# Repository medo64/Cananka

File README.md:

[Cananka](https://medo64.com/cananka/)
======================================

Cananka allows for the computer control of a CAN bus. The control of device is
possible via serial port (SLCAN compatible, Windows/Linux) or via SocketCAN
network driver (Linux). More information about the SLCAN protocol is available
in a [separate document](PROTOCOL.md).

Features:
* USB serial device supporting SLCAN interface
* Supports 1 Mbps CAN bus operation
* Fully isolated (1 kV)
* Does not require CAN bus power supply (onboard DC-to-DC converter)
* 3.81 mm strip headers CAN bus connector
* USB 2.0 interface (type B)

The following hardware version are also available:
* [Mini](https://github.com/medo64/CanankaMini) (USB A connector, non-isolated, and without a case)
* [Framework Expansion Card](https://github.com/medo64/CanankaFEC) (non-isolated, in framework expansion card format)
* [HAT](https://github.com/medo64/CanankaHAT) (intended for Raspberry Pi)

The following additional repositories might be of interest:
* [Firmware](https://github.com/medo64/Cananka.Firmware)
* [Protocol](https://github.com/medo64/Cananka.Firmware/blob/main/PROTOCOL.md)
* [Test software](https://github.com/medo64/Cananka.Software)

---
*You can check my blog and other projects at [www.medo64.com](https://medo64.com/electronics/).*

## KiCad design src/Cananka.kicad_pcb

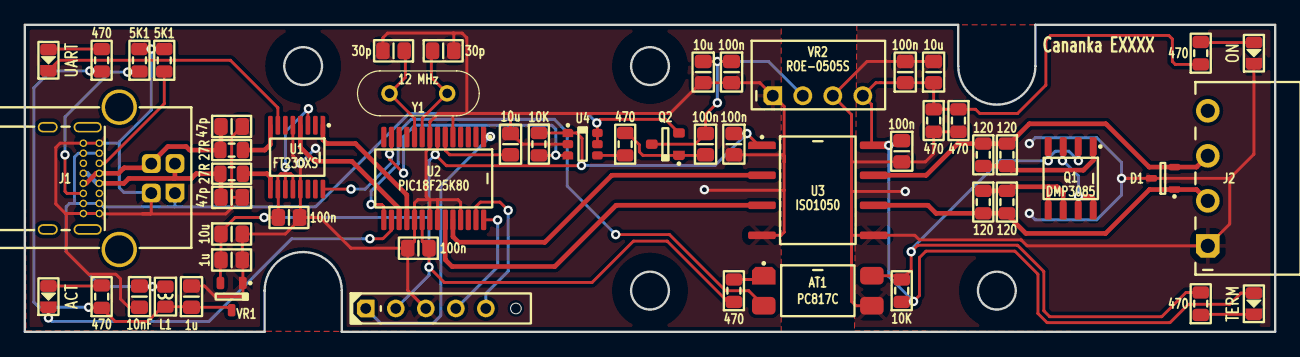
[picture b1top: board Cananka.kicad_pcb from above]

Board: 2 copper layers, 105.8 x 26.0 mm, 55 parts (0 on the bottom side), 40 nets.

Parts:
AT1: PC817C; AT Optocoupler 1ch 80kHz 5000V [817C] (SOP-4)
C1, C2: 30p; C (0805)
C3, C4: 47p; C (0805)
C5: 10nF; C (0805)
C6, C7, C8, C9, C10, C11, C12: 100n; C (0805)
C13, C14: 1u; C (0805)
C15, C16, C17, C18: 10u; C (0805)
D1: PESD24VL2BT; D TVS 24V [PESD24VL2BT,215] (SOT23-3)
DS1: ACT; DS (0805)
DS2: UART; DS (0805)
DS3: TERM; DS (0805)
DS4: ON; DS (0805)
ICSP: Microchip PIC; ICSP PIC Pogo (6w)
J1: USB4085 B1HSW6; J USB BC 2.0 Receptacle (4-16w)
J2: MC 1,5/4; J Phoenix MC [CAN] (4w)
L1: 1u; L (0805)
Q1: DMP3085; Q MOSFET-P x2 (SO-8)
Q2: BSS84; Q MOSFET-P (SOT23-3)
R1, R2: 27R; R (0805)
R3, R4, R5, R6: 120; R (0805)
R7, R8, R9, R10, R11, R12, R13, R14: 470; R (0805)
R15, R16: 5K1; R (0805)
R17, R18: 10K; R (0805)
U1: FT230XS; U Transceiver UART [FT230XS] (SSOP-16)
U2: PIC18F25K80; U Micro [PIC18F25K80] (SSOP-28)
U3: ISO1050; U Transceiver CAN Isolated [ISO1050DUBR] (SOP-8)
U4: 74LVC1T45; U LevelTranslator [74LVC1T45] (SOT23-6)
VR1: MCP1700; VR Linear 3.3V 250mA [MCP1700] (SOT-23)
VR2: ROE-0505S; VR DC-DC Isolated [ROE-0505S] (4w)
Y1: 12 MHz; Y Crystal (HC49U)

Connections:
A_3V3: C6.1, C7.1, C8.1, C14.1, C15.1, ICSP.2, R13.1, R18.1, U1.3, U1.10, U1.11, U1.12, U2.7, U2.20, U3.1, U4.1, VR1.2
A_5V: C13.1, L1.2, R9.1, R10.1, VR1.3
A_5V_SWITCHED: C10.1, C12.1, C17.1, Q2.3, VR2.2
A_5V_USB: C5.1, J1.1, J1.A04, J1.A09, J1.B04, J1.B11, L1.1, Q2.2, U4.5, U4.6
A_CAN_RX: U2.24, U3.2
A_CAN_TX: U2.23, U3.3
A_GND: C1.2, C2.2, C3.2, C4.2, C5.2, C6.2, C7.2, C8.2, C10.2, C13.2, C14.2, C15.2, C16.2, C17.2, ICSP.3, J1.4, J1.A01, J1.A12, J1.B01, J1.B12, R15.2, R16.2, U1.5, U1.13, U2.5, U2.8, U2.19, U2.21, U2.22, U2.25, U3.4, U4.2, VR1.1, VR2.1
A_ICSP_CLK: ICSP.5, U2.27
A_ICSP_DAT: ICSP.4, U2.28
A_IO_TERMINATE#: AT1.2, U2.15
A_ISCP_VPP: ICSP.1, U2.1
A_ISO_TERMINATE: AT1.1, R13.2
A_LED_ACTIVITY: DS1.2, R10.2
A_LED_ACTIVITY#: DS1.1, U2.16
A_LED_UART: DS2.2, R9.2
A_LED_UART#: DS2.1, U1.7
A_OSC1: C1.1, U2.9, Y1.1
A_OSC2: C2.1, U2.10, Y1.2
A_PWREN#: R18.2, U1.16, U2.13, U4.3
A_PWREN#_5V: R14.1, U4.4
A_PWREN#_5V': C12.2, Q2.1, R14.2
A_UART_DN: R2.2, U1.9
A_UART_DP: R1.2, U1.8
A_UART_RX: U1.4, U2.17
A_UART_TX: U1.1, U2.18
A_USB_CC1: J1.A05, R16.1
A_USB_CC2: J1.B05, R15.1
A_USB_DN: C4.1, J1.2, J1.A07, J1.B07, R2.1
A_USB_DP: C3.1, J1.3, J1.A06, J1.B06, R1.1
A_VDDCORE: C16.1, U2.6
B_5V: C9.1, C11.1, C18.1, DS3.2, R7.1, R8.1, R11.1, R17.1, U3.8, VR2.4
B_CAN_H: D1.2, J2.3, R3.1, R4.1, U3.7
B_CAN_H_TERM: Q1.1, R3.2, R4.2
B_CAN_I_TERM: Q1.3, Q1.7, Q1.8
B_CAN_L: D1.1, J2.2, R5.2, R6.2, U3.6
B_CAN_L_TERM: Q1.5, Q1.6, R5.1, R6.1
B_GND: AT1.3, C9.2, C11.2, C18.2, D1.3, DS4.1, J2.1, R7.2, R8.2, U3.5, VR2.3
B_IO_TERMINATE#: AT1.4, Q1.2, Q1.4, R12.2, R17.2
B_LED_POWER: DS4.2, R11.2
B_LED_TERMINATE: DS3.1, R12.1

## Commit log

2016-05-09 Initial version.
2016-05-09 Refactoring.
2016-05-13 Corrected components.
2016-05-15 Updated board to fit official case.
2016-05-15 Refactoring LEDs and adding test points.
2016-05-15 Changed name to match component.
2016-05-15 Moved CAN connector descriptions.
2016-05-15 Added forgotten RESET pullup.
2016-05-15 Added silk screen for SPI.
2016-05-15 Moved fuse to top layer.
2016-05-15 Added a few descriptions.
2016-05-16 Adjusted silk screen.
2016-05-17 Moving descriptions around.
2016-05-17 Added EEPROM settings.
2016-05-23 Added EEPROM flashing description.
2016-05-26 Increasing hole size for 12V->5V VR.
2016-05-26 Swapped VR2 pinout to correct one.
2016-05-26 Refactoring write-protect to use positive logic.
2016-05-26 Refactoring LED placement.
2016-05-27 Adding alternate part.
2016-05-27 Refactoring layout.
2016-05-27 Moving Ext LED source to after fuse.
2016-05-27 Refactoring flood-fill.
2016-06-13 Updating silkscreen and instructions.
2016-06-13 Fixed bug with remote on/off.
2016-08-22 Moving WP wires a bit away.
2017-05-28 Changed bear icon.
2017-06-03 Adjusted icon.
2018-07-08 Moving HAT to a separate directory.
2018-07-09 Added CanStick to USB, USBmini, and USB-RJ45 directories.
2018-07-14 Added termination control and status LED.
2018-08-05 Updated for MPLAB X.
2018-08-06 Refactoring config files.
2018-08-06 Renaming *_init to *_setup where applicable.
2018-08-13 Renamed variable.
2018-08-16 Added screw description.
2018-08-16 Update ICSP connector to be more frendly to pogo pins.
2018-08-16 Added RGB LED anode marking.
2018-08-17 Adding current limiting resistor to optocoupler.
2018-08-17 Removing resistor array to minimize component count.
2018-08-17 Changed MOSFET to a low Vgs one.
2018-08-17 Swaping 10K resistor for 1K to reduce component count at the cost of current.
2018-08-17 Removed controllable termination as it downgrades CAN bus resiliency to transients.
2018-08-17 Updated USBmini to use MCP2221A instead of MCP2221.
2018-08-17 Swapping FT232RL for MCP2221A.
2018-08-17 Minor refactorings.
2018-08-17 Replaced diode for an equivalent one.
2018-08-17 Added UART configuration description.
2018-08-17 Refactoring board to lower component count.
2018-08-17 Sorting out components for easier availability.
2018-08-18 Expanded choice of TVS diode.
2018-08-18 Clock isn't sent out on non-FTDI devices.
2018-08-19 Correct TVS part number.
2018-08-19 Termination is turned on by default on Cananka USBmini.
2018-08-21 TVS diodes a bit closer to the pins.
2018-08-21 Swapped resistor and LED (Active) so all LEDs are pulled the same way.
2018-08-21 Added USBmini schematics.
2018-08-21 Rotating LED to point the same way as the other.
2018-08-22 Added schematics for USB.
2018-08-22 Fixing copper pour on USB/mini.
2018-08-25 Corrected revision file naming.
2018-08-25 Updated read-me with revision history.
2018-08-25 Added extra details for pin configuration.
2018-08-27 Added missing header function.
2018-08-27 PICkit 4 setup.
2018-08-27 Changed USBmini connector to a horizontal one.
2018-08-27 Reorganizing silk screen a bit.
2018-08-27 Updated component part numbers.
2018-08-29 Cleaning up protocol definition.
2018-08-29 Adding reset settings command.
2018-08-29 Fixing extended flags response.
2018-09-01 Reworked software to support SLCAN.
2018-09-01 Added load generator.
2018-09-01 CanankaTest doesn't allow Ctrl+A if there is more than 10000 entries.
2018-09-01 CanankaTest has send functionality.
2018-09-01 CanankaTest has dummy load functionality.
2018-09-02 CanankaTest has setup.
2018-09-02 Refactoring load constants around.
2018-09-02 More light activity during high load.
2018-09-02 CanankaTest has space in application name.
2018-09-02 Placing another resistor on blue LED channel.
2018-09-03 Refactoring device versioning.
2018-09-03 Connecting USBCFG to RC2.
2018-09-03 Load is stopped once CAN bus is closed.
2018-09-03 Refactoring versioning.
2018-09-03 Expanding versioning a bit.
2018-09-03 Updated schematics.
2018-09-04 Added metric screw DigiKey code.
2018-09-16 Moved ground a bit.
2018-09-17 Corrected capacitor count.
2018-09-17 Swapped 22pF capacitors to 0805.
2018-09-18 Termination turned on by default.
2018-09-18 Renamed UartBuffer to CommandBuffer.
2018-09-18 Reworked UART receive to use interrupts.
2018-09-18 Sorting ports based on its numerical value.
2018-09-19 Reworked revision detection.
2018-09-19 Added serial port speed selection.
2018-09-21 Removed support for MCP2562 from USB/mini.
2018-09-21 Made USB/mini board smaller to match CAN connector size.
2018-09-21 Reorientating LEDs.
2018-09-21 Merged schematics update.
2018-10-29 Updated LED count.
2018-10-29 Added version menu item.
2018-10-29 Fixed termination context menu call.
2018-10-29 Extra check for port connection.
2018-10-29 Updated Cananka class.
2018-10-29 Reorganizing directory structure a bit.
2018-10-29 Moving version silkscreen to top.
2018-10-29 Updated version silkscreen.
2018-10-29 Updated protocol links
2018-10-29 Option to save CAN bus settings for the next boot.
2018-10-29 Added option to revert USART speed to default.
2018-10-29 Cananka: Added DebuggerDisplay.
2018-10-29 Added publishing script for software
2018-11-23 Fixed table layout.
2019-07-11 Updated to MPLAB X 5.20 / XC8 2.05
2021-10-01 Adjusted links
2021-10-03 Added new board sized as framework module (not tested)
2021-10-03 Minor refactoring
2021-10-09 Separate pinout for Cananka/framework
2021-11-23 Splintered HAT into a separate repository
2021-11-23 Redesigned Cananka Mini
    * Removed option to power up CAN bus (replaced with jumper)
    * Removed extra LEDs
    * Shortened the board
2021-11-27 Further board size reduction
2021-11-27 Updated serial port configuration
2021-11-27 Reworked to use two MOSFETs for termination
    Needed due to MOSFET's diode passing current when off.
2021-11-28 Updated Cananka Mini schematics
2021-11-28 Fixing bottom solder mask (for protection)
2021-11-28 Updated Cananka to revision E
2021-11-28 Using copper for main panel text
2021-11-28 Removed RJ45 version
2021-11-28 Updated Framework version to E
2021-12-01 Refactoring silk screen
2021-12-01 Added test points for Activity and Terminate lines
2021-12-06 Adjusted to also fit Bud HP-3653-B
2021-12-06 Updated board to use SOIC packages
2022-03-26 Redesigned board for 'Retrofit' outline
2022-03-27 Framework has a split ground to minimize risk of wrong polarity on CAN gnd
2022-04-02 Updated with pinout
2022-04-02 Typo fix
2022-04-04 Updated font to Bahnschrift
2024-02-04 Updated header files
2024-02-04 Updated device type
2024-06-04 Moved firmware to a separate repository
2024-06-04 Moved software to a seaparate repo
2024-06-04 Moved software to a separate repository
2024-06-04 Removing framework files
2024-06-04 Removing 'mini' files
2024-06-16 Switched to KiCAD
2024-06-16 Added soft-start circuit for DC-DC converter
2024-06-16 Added note about other USB connector type
2024-06-20 Added testing V+ output
2024-06-20 Added assembly title
2024-06-23 Updated crystal circuit
2024-07-28 Updated refdes
2024-09-03 Removed external power supply
2024-09-05 Fixed pwren# line behavior
2024-09-05 Moved FTProg template
2024-09-08 Fixing termination MOSFET connections
2024-09-08 Increasing termination resistor value
2024-11-03 Updated ISO1050 footprint
2024-11-03 Added enclosure
2024-11-08 Moving optocoupler to 3V3 line
2024-11-18 Adjusted resistors a bit
